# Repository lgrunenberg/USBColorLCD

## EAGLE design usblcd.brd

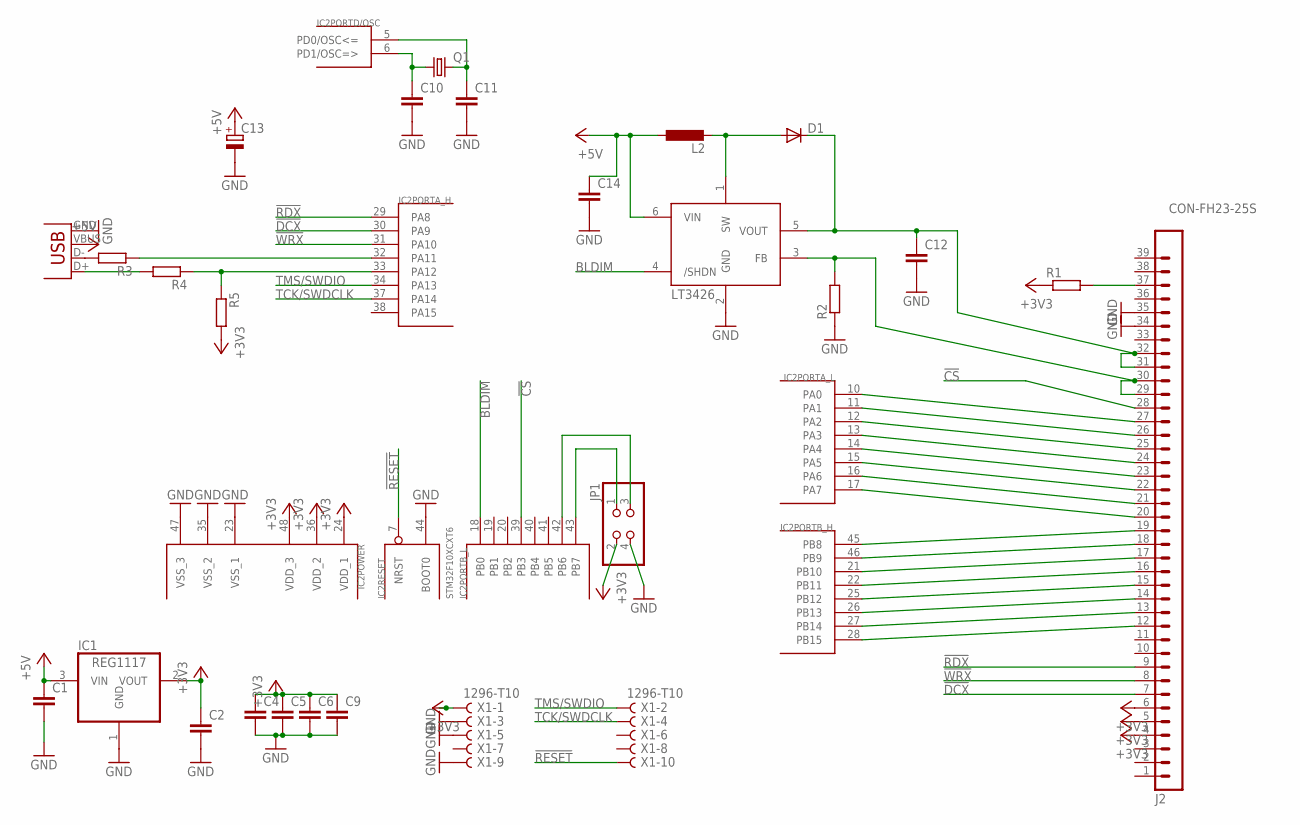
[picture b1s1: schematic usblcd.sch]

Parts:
C1, C2, C4, C6, C9, C10, C11, C14: C-EUC0603; C0603
C5, C12: C-EUC0805; C0805
C13: CPOL-EUC; PANASONIC_C
D1: DIODE-SOD323-W; SOD323-W
IC1: REG1117; SOT223
IC2: STM32F10XCXT6; TQFP48
J2: CON-FH23-25S; FH23-25S
JP1: PINHD-2X2_2.54-SMD; 2X02SMD
L2: L-EUL3230M; L3230M
Q1: CRYSTALCTS406; CTS406
R1, R2, R3, R4, R5: R-EU_R0603; R0603
U$4: LT3426; SOT23-6
X1: 1296-T10; 1296-10
X2: USB-MICROB

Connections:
!CS: IC2.39 (PB3), J2.28
!DCX: IC2.30 (PA9), J2.7
!RDX: IC2.29 (PA8), J2.9
!RESET: IC2.7 (NRST), X1.10
!WRX: IC2.31 (PA10), J2.8
+3V3: C2.1, C4.1, C5.1, C6.1, C9.1, IC1.2 (VOUT), IC2.24 (VDD_1), IC2.36 (VDD_2), IC2.48 (VDD_3), J2.4, J2.5, J2.6, JP1.2, R1.1, R5.2, X1.1
+5V: C1.1, C13.+, C14.1, IC1.3 (VIN), L2.1, U$4.6 (VIN), X2.VBUS
BLDIM: IC2.18 (PB0), U$4.4 (/SHDN)
GND: C1.2, C2.2, C4.2, C5.2, C6.2, C9.2, C10.2, C11.2, C12.2, C13.-, C14.2, IC1.1 (GND), IC2.23 (VSS_1), IC2.35 (VSS_2), IC2.44 (BOOT0), IC2.47 (VSS_3), J2.34, J2.35, JP1.4, R2.1, U$4.2 (GND), X1.3, X1.5, X1.9, X2.GND
unnamed: IC2.16 (PA6), J2.21
unnamed: IC2.15 (PA5), J2.22
unnamed: IC2.14 (PA4), J2.23
unnamed: IC2.13 (PA3), J2.24
unnamed: IC2.12 (PA2), J2.25
unnamed: IC2.11 (PA1), J2.26
unnamed: IC2.10 (PA0), J2.27
unnamed: IC2.32 (PA11), R3.1
unnamed: IC2.27 (PB14), J2.13
unnamed: IC2.26 (PB13), J2.14
unnamed: IC2.25 (PB12), J2.15
unnamed: IC2.22 (PB11), J2.16
unnamed: IC2.21 (PB10), J2.17
unnamed: IC2.46 (PB9), J2.18
unnamed: IC2.45 (PB8), J2.19
unnamed: IC2.17 (PA7), J2.20
unnamed: IC2.28 (PB15), J2.12
unnamed: C10.1, IC2.6 (PD1/OSC=>), Q1.1
unnamed: C11.1, IC2.5 (PD0/OSC<=), Q1.3 (2)
unnamed: R3.2, X2.D-
unnamed: R4.2, X2.D+
unnamed: IC2.33 (PA12), R4.1, R5.1
unnamed: D1.A, L2.2, U$4.1 (SW)
unnamed: C12.1, D1.C, J2.31, J2.32, U$4.5 (VOUT)
unnamed: J2.29, J2.30, R2.2, U$4.3 (FB)
unnamed: J2.37, R1.2
SCL: IC2.42 (PB6), JP1.3
SDA: IC2.43 (PB7), JP1.1
TCK/SWDCLK: IC2.37 (PA14), X1.4
TMS/SWDIO: IC2.34 (PA13), X1.2
VBAT: IC2.1 (VBAT)
VDDA: IC2.9 (VDDA)
VSSA: IC2.8 (VSSA)

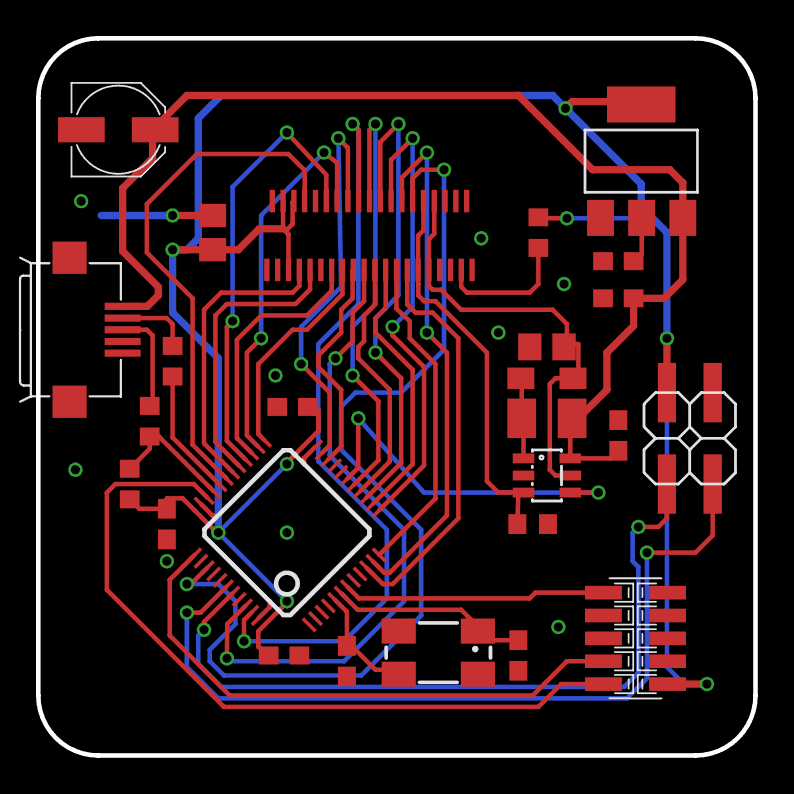
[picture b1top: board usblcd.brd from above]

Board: 2 copper layers, 39.8 x 39.8 mm, 26 parts (0 on the bottom side), 39 nets.

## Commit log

2016-03-15 Added files via upload
